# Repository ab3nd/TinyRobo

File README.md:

# TinyRobo
Hardware and software for a tiny robot platform based on the ESP-8266 WiFi modules and hacked children's toys. 

## Installation 

git clone https://github.com/ab3nd/TinyRobo

cd TinyRobo/software/catkin_ws/

sudo apt-get install libmagick++-dev

sudo ln -s /usr/include/ImageMagick-6/ /usr/include/ImageMagick

sudo apt-get install libmagickcore-dev

sudo apt-get install libmagickwand-6.q16-2

sudo apt-cache search libMagick++

sudo apt-get install libmagick++-6.q16-5v5

sudo apt-get install libmagick++-6.q16-dev  libmagickcore-dev libmagick++-dev

sudo ln -s /usr/lib/x86_64-linux-gnu/libMagickCore-6.Q16.so /usr/lib/x86_64-linux-gnu/libMagickCore.so

sudo ln -s /usr/lib/x86_64-linux-gnu/libMagick++-6.Q16.so /usr/lib/x86_64-linux-gnu/libMagick++.so

I've recently switched to using http://wiki.ros.org/aruco_detect (although https://github.com/pal-robotics/aruco_ros can probably do a lot of the same things). When I remove my attempt at making a simulator and my modded version of APRIL tags, the dependencies of this section will change a lot.

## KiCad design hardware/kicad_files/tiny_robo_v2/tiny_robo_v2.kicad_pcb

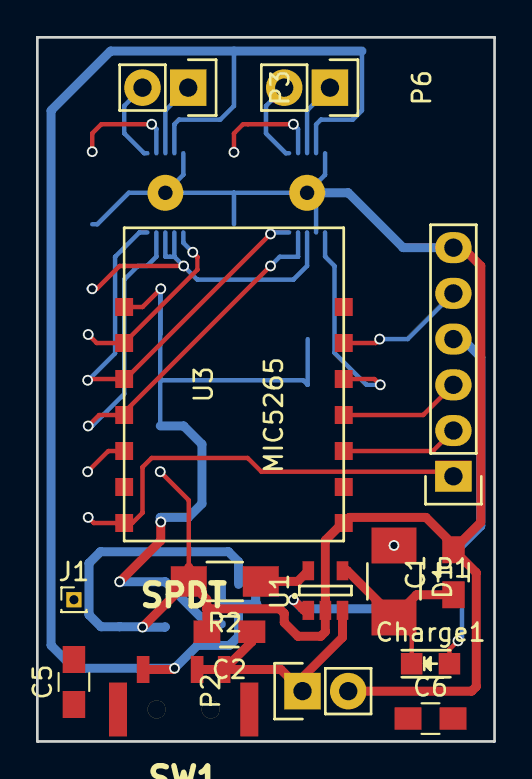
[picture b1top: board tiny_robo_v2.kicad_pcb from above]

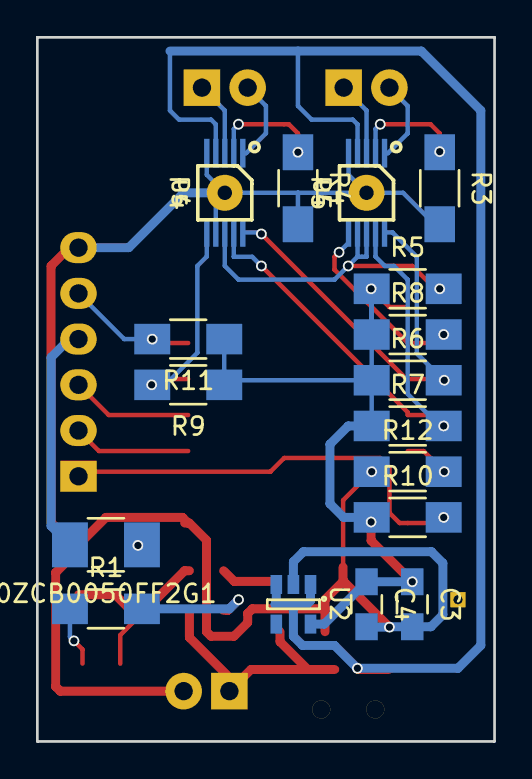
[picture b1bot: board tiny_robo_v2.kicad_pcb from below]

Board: 2 copper layers, 25.4 x 39.1 mm, 34 parts (19 on the bottom side), 25 nets.

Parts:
0ZCB0050FF2G1: Thermal fuse; R_1210_HandSoldering
C1, C2: 4.7uF; C_0805_HandSoldering
C3, C5, C6: 0.1uF; C_0805_HandSoldering
C4: 10uF; C_0805_HandSoldering
Charge1: LED; LED_0805
D1: GF1A; R_1210_HandSoldering
J1: Conn_01x01; Pin_Header_Straight_1x01_Pitch1.00mm
P1: CONN_01X06; Pin_Header_Straight_1x06
P2, P3: CONNECTOR; Pin_Header_Straight_1x02
P4: BATT; SolderWirePad_single_0-8mmDrill
P5: CONN_01X02; SolderWirePad_single_0-8mmDrill
P6: CONN_01X02; Pin_Header_Straight_1x02
R1, R3, R5, R6, R9, R12: 10k; R_1206_HandSoldering
R2: 470; R_1206_HandSoldering
R4: 2k; R_1206_HandSoldering
R7, R8: 0.22; R_1206_HandSoldering
R10, R11: 1k; R_1206_HandSoldering
SW1: SPDT; spdt_pcm12stmr
U1: MCP73831; SOT-23-5
U2: ESP8266-ESP-03; SOT-23-5
U3: MIC5265; ESP8266-ESP-03
U4, U5: DRV8830; MSOP10

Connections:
5Vin: 0ZCB0050FF2G1.2, P1.4
+3.3V: C3.1, C4.1, R1.1, R3.1, R5.1, R9.1, R10.1, R11.1, R12.1, U3.5
+BATT: C2.1, P4.1, SW1.2, SW1.3, U1.3
Fault1: U2.5, U5.6
Fault2: R12.2, U4.6
GND: C1.2, C2.2, C3.2, C4.2, C5.2, C6.2, P1.6, P2.1, P3.1, R4.2, R6.1, R7.2, R8.2, U1.2, U2.1, U3.2, U4.5, U5.5, U5.7
unnamed: 0ZCB0050FF2G1.1, D1.1
unnamed: C1.1, Charge1.1, D1.2, U1.4
unnamed: Charge1.2, R2.1
unnamed: J1.1, R5.2
unnamed: P1.1, R1.2
unnamed: P1.2, U2.3
unnamed: P1.3, U2.4
unnamed: P1.5, R3.2
unnamed: P5.1, U4.3
unnamed: P6.1, U5.3
unnamed: P6.2, U5.1
unnamed: R2.2, U1.1
unnamed: R4.1, U1.5
unnamed: R7.1, U4.2
unnamed: R8.1, U5.2
unnamed: R9.2, U4.7, U4.8, U5.8
SCL: R10.2, U4.10, U5.10
SDA: R11.2, U4.9, U5.9
Unreg: C5.1, C6.1, SW1.1, U3.1, U3.3, U4.4, U5.4

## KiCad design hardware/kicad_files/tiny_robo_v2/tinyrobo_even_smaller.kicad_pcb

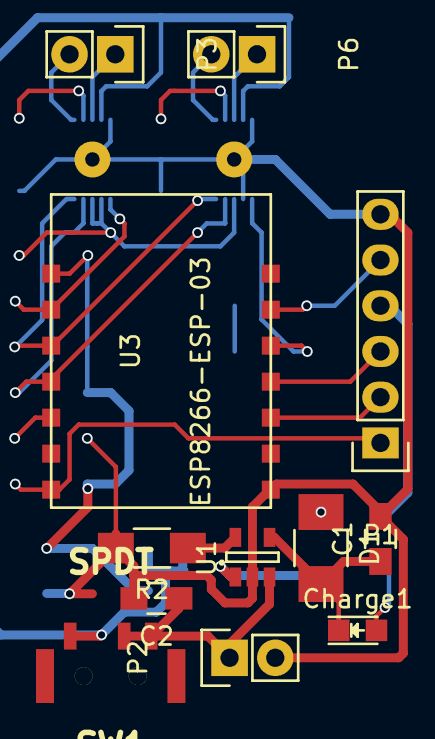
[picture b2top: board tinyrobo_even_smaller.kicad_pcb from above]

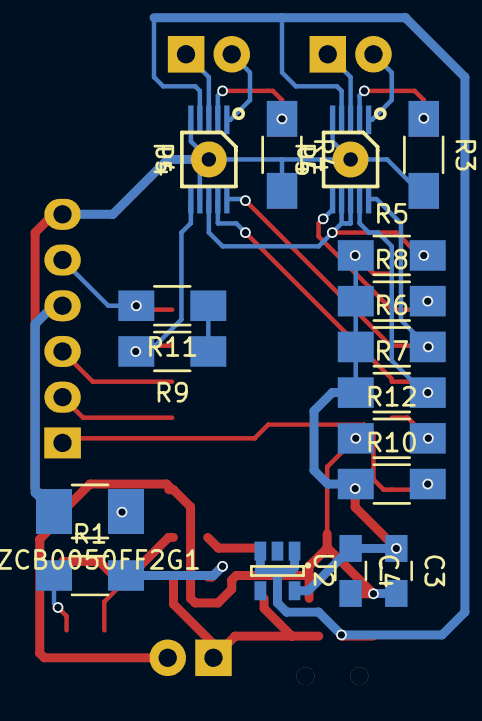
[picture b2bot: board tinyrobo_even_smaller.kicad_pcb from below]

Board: 2 copper layers, 31 parts (19 on the bottom side), 26 nets.

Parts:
0ZCB0050FF2G1: Thermal fuse; R_1210_HandSoldering
C1, C2: 4.7uF; C_0805_HandSoldering
C3: 0.1uF; C_0805_HandSoldering
C4: 10uF; C_0805_HandSoldering
Charge1: LED; LED_0805
D1: GF1A; R_1210_HandSoldering
P1: CONN_01X06; Pin_Header_Straight_1x06
P2: BATT; Pin_Header_Straight_1x02
P3, P6: CONN_01X02; Pin_Header_Straight_1x02
P4, P5: CONNECTOR; SolderWirePad_single_0-8mmDrill
R1: 470; R_1206_HandSoldering
R2: 2k; R_1206_HandSoldering
R3, R4: 0.22; R_1206_HandSoldering
R5, R8, R9, R10, R11, R12: 10k; R_1206_HandSoldering
R6, R7: 1k; R_1206_HandSoldering
SW1: SPDT; spdt_pcm12stmr
U1: MCP73831; SOT-23-5
U2: MIC5265; SOT-23-5
U3: ESP8266-ESP-03
U4, U5: DRV8830; MSOP10

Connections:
5Vin: 0ZCB0050FF2G1.2, P1.4
+3.3V: C3.1, C4.1, R5.1, R6.1, R7.1, R8.1, R9.1, R10.1, R11.1, U2.5, U3.8
+BATT: C2.1, P2.1, SW1.2, SW1.3, U1.3
Fault1: R9.2, U3.5, U5.6
Fault2: R8.2, U3.9, U4.6
GND: C1.2, C2.2, C3.2, C4.2, P1.6, P2.2, P4.1, P5.1, R2.2, R3.2, R4.2, R12.1, U1.2, U2.2, U3.1, U4.5, U5.5, U5.7
unnamed: 0ZCB0050FF2G1.1, D1.1
unnamed: C1.1, Charge1.1, D1.2, U1.4
unnamed: Charge1.2, R1.1
unnamed: P1.1, R10.2, U3.14
unnamed: P1.2, U3.3
unnamed: P1.3, U3.4
unnamed: P1.5, R11.2, U3.6
unnamed: P3.1, U4.3
unnamed: P3.2, U4.1
unnamed: P6.1, U5.3
unnamed: P6.2, U5.1
unnamed: R1.2, U1.1
unnamed: R2.1, U1.5
unnamed: R3.1, U4.2
unnamed: R4.1, U5.2
unnamed: R5.2, U4.7, U4.8, U5.8
unnamed: R12.2, U3.12
SCL: R6.2, U3.10, U4.10, U5.10
SDA: R7.2, U3.11, U4.9, U5.9
Unreg: SW1.1, U2.1, U2.3, U4.4, U5.4

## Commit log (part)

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2018-03-24 added skeleton for dedupe script, some edits
2018-03-24 commented out duplicate lines
2018-03-25 developed a few sections, building lags my computer now...
2018-03-26 removed skeleton files for participants that Dalton is coding
2018-03-26 cleaned up old stats scripts that I'm not using
2018-03-26 added json data files
2018-03-26 adding some code for working with the whole data set
2018-03-27 Coding
2018-03-29 old thesis file conflicts
2018-03-30 updated diary
2018-03-30 thesis edits
2018-03-30 spelling
2018-04-02 expanded UI section
2018-04-06 removed old compiler files
2018-04-06 changed runner and gcpr code to add 'self.'
2018-04-06 got single robot to turn to heading and start moving
2018-04-07 working for 6 robots, but buggy
2018-04-09 still gets stuck in corners
2018-04-10 draws space properly
2018-04-10 draws vectors, removed corners
2018-04-10 finally have the coordinates right
2018-04-10 Headings per grid square
2018-04-11 isBetween getting better
2018-04-11 Wider path working
2018-04-11 use nearest points rather than next nearest
2018-04-11 added point interpolation, doesn't seem to be needed
2018-04-11 fixed bad angle calculation
2018-04-13 using decomp to move in space
2018-04-15 degarbaged the heading math, it was apparently trash hax
2018-04-16 Added 10 jsons(pids 31-40). P32->task 4->gesture 6 likely has an incorect time stamp. I can't verify it at this time. I'll verify it when I can.
2018-04-17 still wedges on +/- pi discontinuity
2018-04-19 Dispersion controller, executes but doesnt seem to send program correctly
2018-04-22 scripts for working on the data
2018-04-23 section on space decomposition and coordinate systems
2018-04-25 further attempts at statistical relevance
2018-04-25 prettified json and updated json combiner
2018-04-27 more user data
2018-05-01 fixed typos and thinkos in user data files, mostly missing -o flags on 'other' codes
2018-05-01 combined all data into single json
2018-05-02 data to paper, loading per-task data
2018-05-11 adds data, scripts for working with it
2018-05-15 basic re and base cunning, no NLTK needed
2018-05-15 converts user actions to a string, for edit distance checks
2018-05-17 Added scripts p31 through p40. p35 is missing? Though it was coded, there's a json for it.
2018-05-29 some data analysis, adds motor debug driver skeleton
2018-05-29 adds launchfile for live ui
2018-05-30 adds dot to middle of recognized tags
2018-06-01 now seems to have enough info to get values
2018-06-02 seperated driving to point and point conversion
2018-06-04 resolves some syntax, copy/paste errors
2018-06-06 hurf durf integer range is +/-127, not +/-128
2018-06-08 more plots, more anovas
2018-06-20 automating as much selection classification as possible
2018-06-20 handles all classes of events
2018-06-20 support for H1 in, support for H2 in process
2018-06-22 graphing results, found some bugs and fixed them, which made the results more confusing
2018-06-24 turning notes into text
2018-06-24 Added appendix and some figures
2018-06-27 Paper edits, some work on tap sequences to determine if people tapped all ten robots to select them (one guy did, most people don't)
2018-06-28 wrote a script to label all sections and applied it
2018-06-28 Revert "wrote a script to label all sections and applied it"
    This reverts commit fb39c66dee5e4b273aa33995653af81e22065f3a.
2018-06-28 Revert "Script somehow still munges files"
    This reverts commit b0904efeac673e58866820f581c711f8db4f7dc7.
2018-06-28 Now the script works, and smart-quotes have been lobotomized
2018-06-28 first use of new refs
2018-07-03 lots of data on non-selection gestures
2018-07-06 added strategy stuff for formations
2018-07-06 adding untracked jupyter notebook
2018-07-10 combined all raw files to add selection, position, interface tags
2018-07-11 started debugging, but won't have time
2018-07-11 finished marking for classes
2018-07-13 clean up and organization
2018-07-15 images for paper
2018-07-17 graphics, plus writing and trying to figure out ui uses
2018-07-20 more conclusive conclusion paragraph, some edits
2018-07-22 edits about UI widgetry
2018-07-24 minor edits
2018-08-01 full screen with window title bar (the hard way)
2018-08-01 Gets strokes from user inputs on screen
2018-08-01 seems to be running thread, but very laggy
2018-08-02 Best solution so far, but remember: python threads aren't
2018-08-06 Don't do updates while being touched, does a much better job getting all touches
2018-08-07 trying to get my head around destuttering again
2018-08-08 still needs testing
2018-08-09 Destutterer seems to be relatively stable and publishes stroke messages
2018-08-09 first commit of box detector
2018-08-09 added stroke dump for stroke messages
2018-08-10 adding a bunch of ui support scripts
2018-08-10 box select working a little better
2018-08-14 fixed problem in box select detection
2018-08-14 seems to be about right, needs work on point membership test
2018-08-15 Min bounding ellipse for lasso select cleaned up printfs
2018-08-15 tap working, stroke destutterer seems to sometimes publish strokes over and over
2018-08-17 tap waypoint detector
2018-08-23 detectors for various UI events
2018-08-23 checked path vs select and box/drag ambiguity fixes
2018-08-27 premerge
2018-08-29 recorded noise from tag noise bags
2018-09-05 about to start testing figure 8 code
2018-09-06 adds motor test visualization script
2018-09-07 I think I had a roll/yaw confusion due to camera coordinate roll being body coordinate yaw
2018-09-10 description of robot experiment
2018-09-10 data for a bunch of runs of various robots
2018-09-12 adds bags and rendering script
2018-09-12 renders all of them, changing to render by ID
2018-09-13 major edits, less despair about badness of hardware
2018-09-17 basic connection of space decomposer to gcpr prog distributor
2018-09-18 adds more compiler code and camera for argos
2018-09-19 trying to set up scripts for argos launch from launchfile
2018-09-19 uses rotated tag images now
2018-09-20 GCPR program sending to limited set of robots works, needs new predicates for infinite space
2018-09-23 point mapper is a mess in sim, added a new sim version
2018-09-23 sim image is same size as screen, don't resize in kivy
2018-09-24 first step in fixing the tech debt around image sizes, live ui now uses resized image
2018-09-24 fixing tech debt, part 2, now the system is running on the big image
2018-09-25 notes on validation
2018-09-27 added some thoughts about revisions on how compiler works
2018-09-27 adds a message file I missed and an end-cmd detector
2018-09-27 reduced spurious path detections
2018-09-27 removed unneeded fake laser service, ArGOS provides that
2018-10-01 non-oval lasso select
2018-10-02 adds code generation and write-up of modfied bug algo
2018-10-04 adds tangent bug in gcpr, not yet tested
2018-10-05 removed data
2018-10-05 moved proposed_work.txt into what I actually did
2018-10-05 fixed some formatting, section placement, less-than signs
2018-10-05 ros messaging doesn't seem to work, rebooting computer to see if it comes back
2018-10-05 adds description of the loopback setup
2018-10-06 turn to goal and approach it, nothing else
2018-10-06 turns in the right directions, but still hits wall
2018-10-06 does obstacle avoid, but not edge follow
2018-10-07 got alignment to edge, about to try moving forward
2018-10-07 basic follow for edges, leaves corners
2018-10-07 can do edge follow, but tends to get loose eventually
2018-10-08 cleaner handling of corners, but doesn't follow edges perfectly
2018-10-09 still don't have a very good edge follow
2018-10-10 added more notes
2018-10-11 turning notes into proof/expansion
2018-10-13 if you can precisely interact in teh world, use that to do your tasks instead of your chump robots
2018-10-14 attempts to remove spurious waypoints
2018-10-15 changed destutter threshold to try to eliminate bad waypoint tap detection
2018-10-15 decent obstacle avoid, but gets into trap corridors
2018-10-16 notes on SCT
2018-10-17 updated refs in related work chapter
2018-10-17 adds missing tex files
2018-10-17 added stuff on noncomputing swarms
2018-10-18 lots of edits, started writing more conclusive conclusion
2018-10-19 adding image
2018-10-20 added 11th hour 3d print body design
2018-10-21 modified a few dimensions
2018-10-21 dispersion in, formal def looking ok
2018-10-21 some bugfixes, can't combine taps and paths or else disperse gets weird
2018-10-22 extended language to include point info, for passthrough to compiler
2018-10-22 using gpio2 as a gpio is... troublesome
2018-10-23 motors were still a little tight, added 0.1mm
2018-10-23 Updated schematic, board probably needs relayout (after I graduate).
2018-10-24 added some notes
2018-10-24 edits describing new robots, should probably include a picture
2018-10-24 fixed a few todos
2018-10-26 wrote up compiler internals
2018-10-26 most of the compiler GCPR stage
2018-10-28 Code in for everything, but it's probably bad. Fix Sunday
2018-10-30 fixed some of the section placement of images in the appendix
2018-10-30 more notes on verification, I don't think the compiler itself is what needs verifying
2018-10-31 messing around with modified tangent bug
2018-11-05 conclusion now a bit more conclusive
2018-11-07 draft disperse, object avoid needs to be better
2018-11-07 this disperse works, but looks bad if the distance is set to high (pin to walls)
2018-11-08 fixes for path values, proper retreival and extending the language to let them be negative
2018-11-09 wedge-free travel, but doesn't follow edges
2018-11-09 almost wall follows, but hangs in corners
2018-11-09 updates reach and follow points, so good for checking leave condtdition
2018-11-09 detection of leave condition looks good
2018-11-12 Adds image
2018-11-12 more paper edits, including reader feedback
2018-11-12 added a couple of todos for sections to explain
2018-11-13 more in translation section, still feels a little light
2018-11-13 adds new paper on bug algos for swarm robots
2018-11-15 minor fixes, esp. to captions for figures
2018-11-15 adds needed ieee template file
2018-11-19 More GCPR bug tweaks
2018-11-21 which vs that
2018-11-21 fixed fixed doubled doubled words words (thanks thanks grep grep)
2018-11-26 singlspaced bib, some of Holly's edits
2018-11-26 debritishified spellings
2018-11-26 top right page number on all pages, abstract under 350 words
2018-11-27 adds top down view and arena images
2018-11-28 Holly edits round 3
2018-11-30 modified end of ch on hw to reflect hypothesis about hardware
2018-12-02 adds overhead image
2018-12-07 initial commit of chopper
2018-12-07 writes bagfiles
2018-12-11 training and weird ui section
2018-12-22 merry christmas abe
2018-12-23 Section on advanced gestures
2019-01-02 needs more detail on commands
2019-01-03 More on gcpr command implementation
2019-01-08 gets time spans from coding
2019-01-09 adds other gesture list for writeup
2019-01-09 looking into timing calculation, but need data
2019-01-10 adds more of the time check, not yet tested
2019-01-15 adding missing argos worlds
2019-01-16 from home
2019-01-16 pixel-location only
2019-01-16 color threshold not perfect yet
2019-01-22 contour detection beats blob detection
2019-01-22 skeleton all there, need working install to finish
2019-01-26 adds section on UI testing, no values in yet
2019-01-26 fixed offsets in bag chopper
2019-01-26 reindexed all the generated bags
2019-01-26 Fixes to the bagfile handling, and the bagfiles themselves (reindex)
2019-01-26 reindexed. A. B. I. Always Be Indexing
2019-01-26 test framework
2019-01-27 adds converter from what was logged (Point) to what is needed (Kivy_Event)
2019-01-27 test system appears to be working, stashes files, checked contour check forregion test case
2019-01-29 closing on timing error with bagfiles
2019-01-30 images and bags and such for the debugged recognizer test run
2019-01-30 changed to handle subdir
2019-02-01 put the files back
2019-02-04 got compiler test working
2019-02-05 adding data from analysis, initial writeup
2019-02-06 added last chapter file
2019-02-19 Holly edits
2019-02-24 paragraph on NASA as high-training environment
2019-03-09 final proofreading
